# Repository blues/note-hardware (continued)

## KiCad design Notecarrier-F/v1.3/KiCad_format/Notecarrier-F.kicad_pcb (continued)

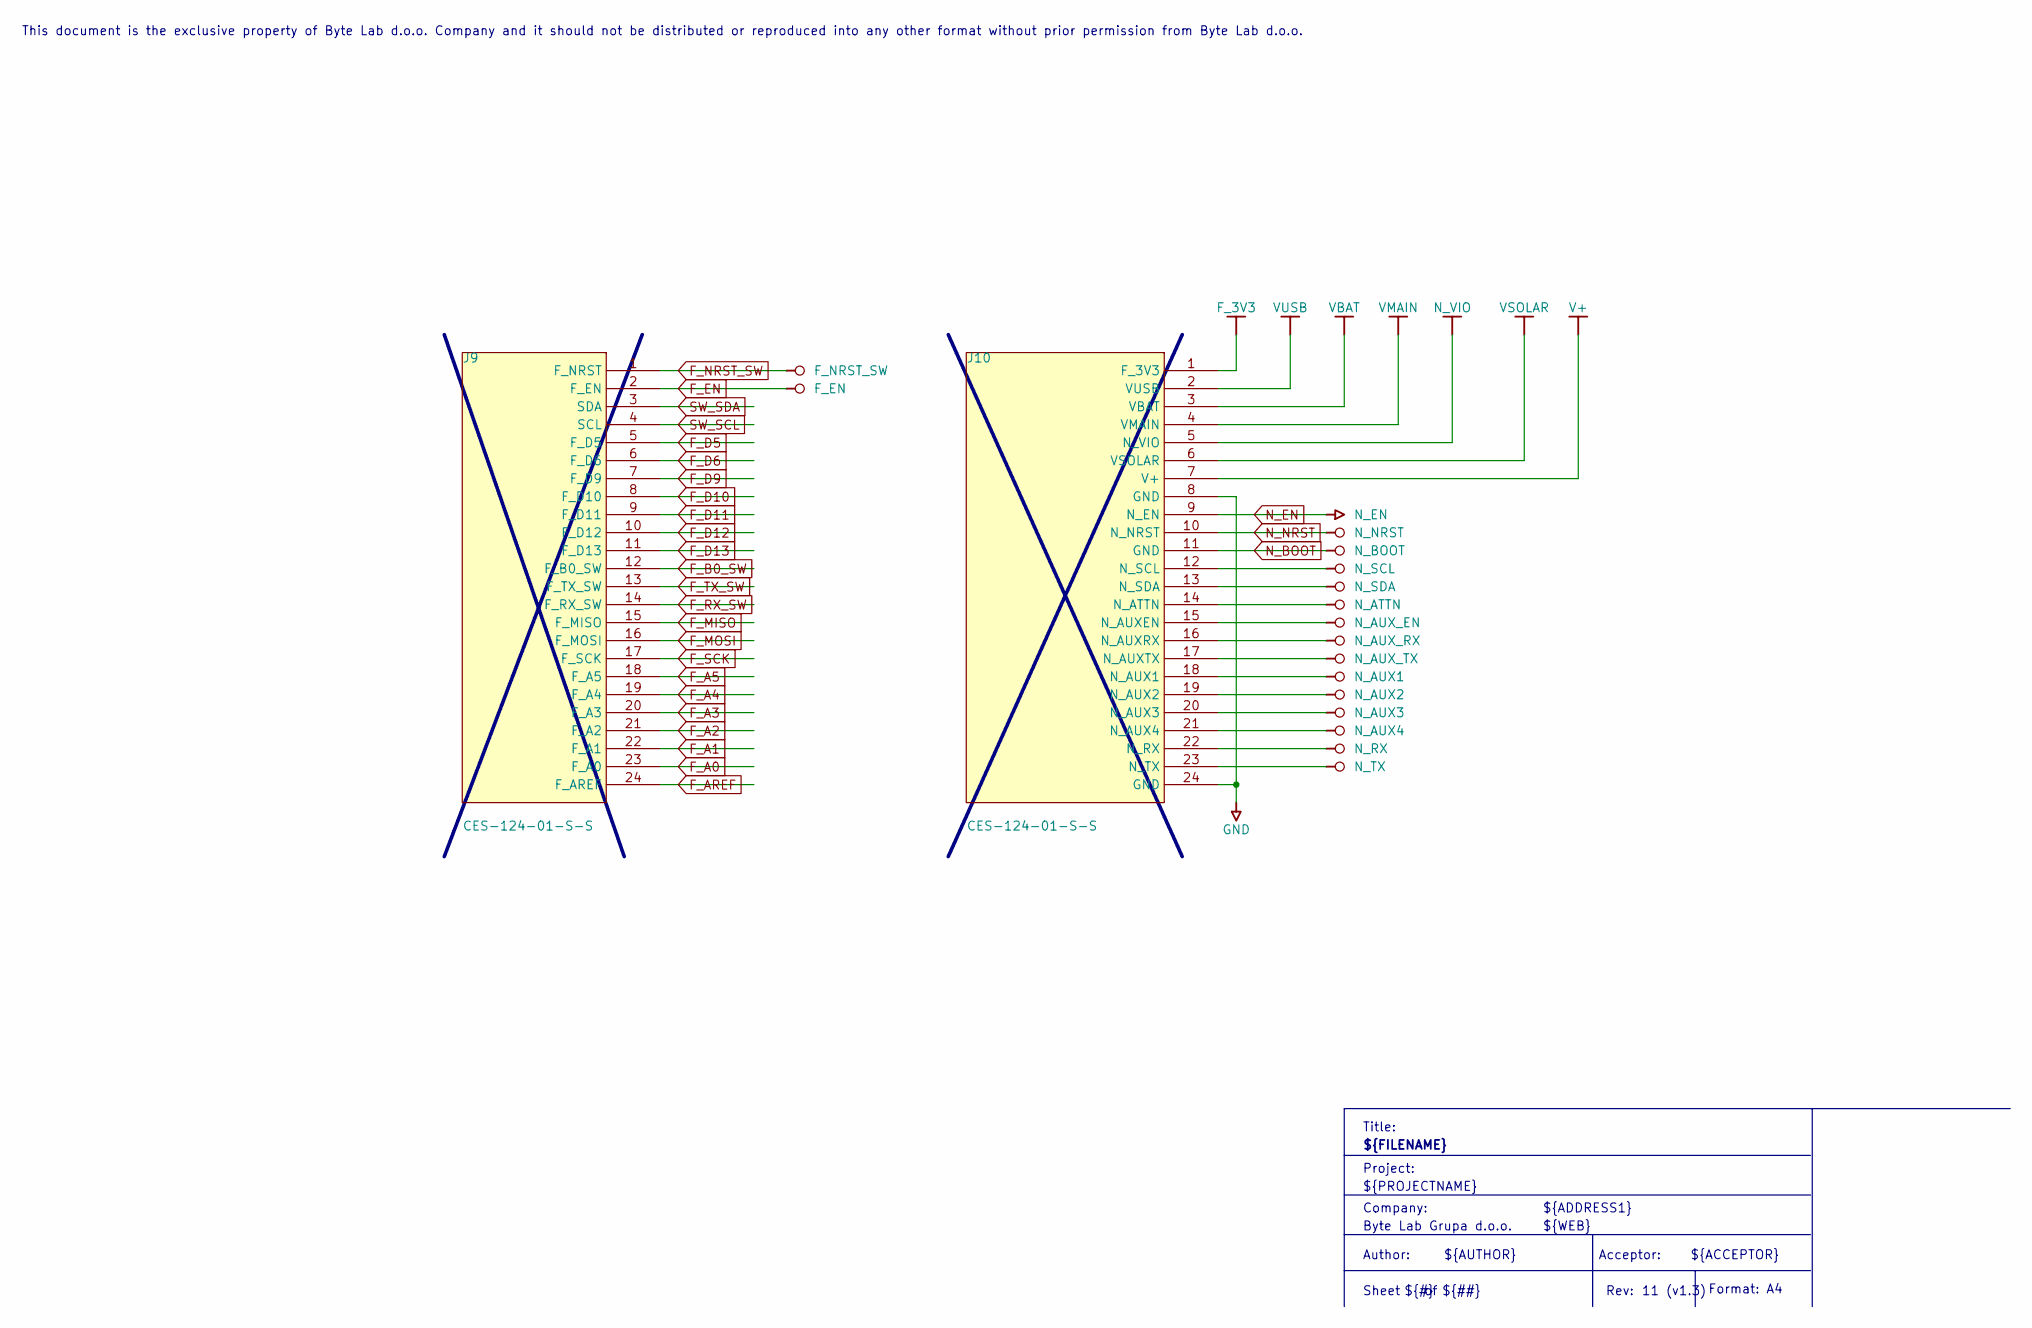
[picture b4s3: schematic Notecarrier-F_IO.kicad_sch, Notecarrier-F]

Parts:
J9, J10: CES-124-01-S-S; MANUFACTURER PART NUMBER CES-124-01-S-S

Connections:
F_3V3: J10.1 (F_3V3); also elsewhere on the board
F_A0: J9.23 (F_A0); also elsewhere on the board
F_A1: J9.22 (F_A1); also elsewhere on the board
F_A2: J9.21 (F_A2); also elsewhere on the board
F_A3: J9.20 (F_A3); also elsewhere on the board
F_A4: J9.19 (F_A4); also elsewhere on the board
F_A5: J9.18 (F_A5); also elsewhere on the board
F_AREF: J9.24 (F_AREF); also elsewhere on the board
F_B0_SW: J9.12 (F_B0_SW); also elsewhere on the board
F_D5: J9.5 (F_D5); also elsewhere on the board
F_D6: J9.6 (F_D6); also elsewhere on the board
F_D9: J9.7 (F_D9); also elsewhere on the board
F_D10: J9.8 (F_D10); also elsewhere on the board
F_D11: J9.9 (F_D11); also elsewhere on the board
F_D12: J9.10 (F_D12); also elsewhere on the board
F_D13: J9.11 (F_D13); also elsewhere on the board
F_EN: J9.2 (F_EN); also elsewhere on the board
F_MISO: J9.15 (F_MISO); also elsewhere on the board
F_MOSI: J9.16 (F_MOSI); also elsewhere on the board
F_NRST_SW: J9.1 (F_NRST); also elsewhere on the board
F_RX_SW: J9.14 (F_RX_SW); also elsewhere on the board
F_SCK: J9.17 (F_SCK); also elsewhere on the board
F_TX_SW: J9.13 (F_TX_SW); also elsewhere on the board
GND: J10.8 (GND), J10.24 (GND); also elsewhere on the board
N_ATTN: J10.14 (N_ATTN); also elsewhere on the board
N_AUX1: J10.18 (N_AUX1); also elsewhere on the board
N_AUX2: J10.19 (N_AUX2); also elsewhere on the board
N_AUX3: J10.20 (N_AUX3); also elsewhere on the board
N_AUX4: J10.21 (N_AUX4); also elsewhere on the board
N_AUX_EN: J10.15 (N_AUXEN); also elsewhere on the board
N_AUX_RX: J10.16 (N_AUXRX); also elsewhere on the board
N_AUX_TX: J10.17 (N_AUXTX); also elsewhere on the board
N_BOOT: J10.11 (GND); also elsewhere on the board
N_EN: J10.9 (N_EN); also elsewhere on the board
N_NRST: J10.10 (N_NRST); also elsewhere on the board
N_RX: J10.22 (N_RX); also elsewhere on the board
N_SCL: J10.12 (N_SCL); also elsewhere on the board
N_SDA: J10.13 (N_SDA); also elsewhere on the board
N_TX: J10.23 (N_TX); also elsewhere on the board
N_VIO: J10.5 (N_VIO); also elsewhere on the board
SW_SCL: J9.4 (SCL); also elsewhere on the board
SW_SDA: J9.3 (SDA); also elsewhere on the board
V+: J10.7 (V+); also elsewhere on the board
VBAT: J10.3 (VBAT); also elsewhere on the board
VMAIN: J10.4 (VMAIN); also elsewhere on the board
VSOLAR: J10.6 (VSOLAR); also elsewhere on the board
VUSB: J10.2 (VUSB); also elsewhere on the board

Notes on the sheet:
${AUTHOR}
${#}
${PROJECTNAME}
Title:
Author:
Sheet
Company:
${##}
Format: A4
Project:
${ACCEPTOR}
${ADDRESS1}
${REVISION}
This document is the exclusive property of Byte Lab d.o.o. Company and it should not be distributed or reproduced into any other format without prior permission from Byte Lab d.o.o.
${FILENAME}
Rev:
${COMPANY}
${WEB}
Acceptor:

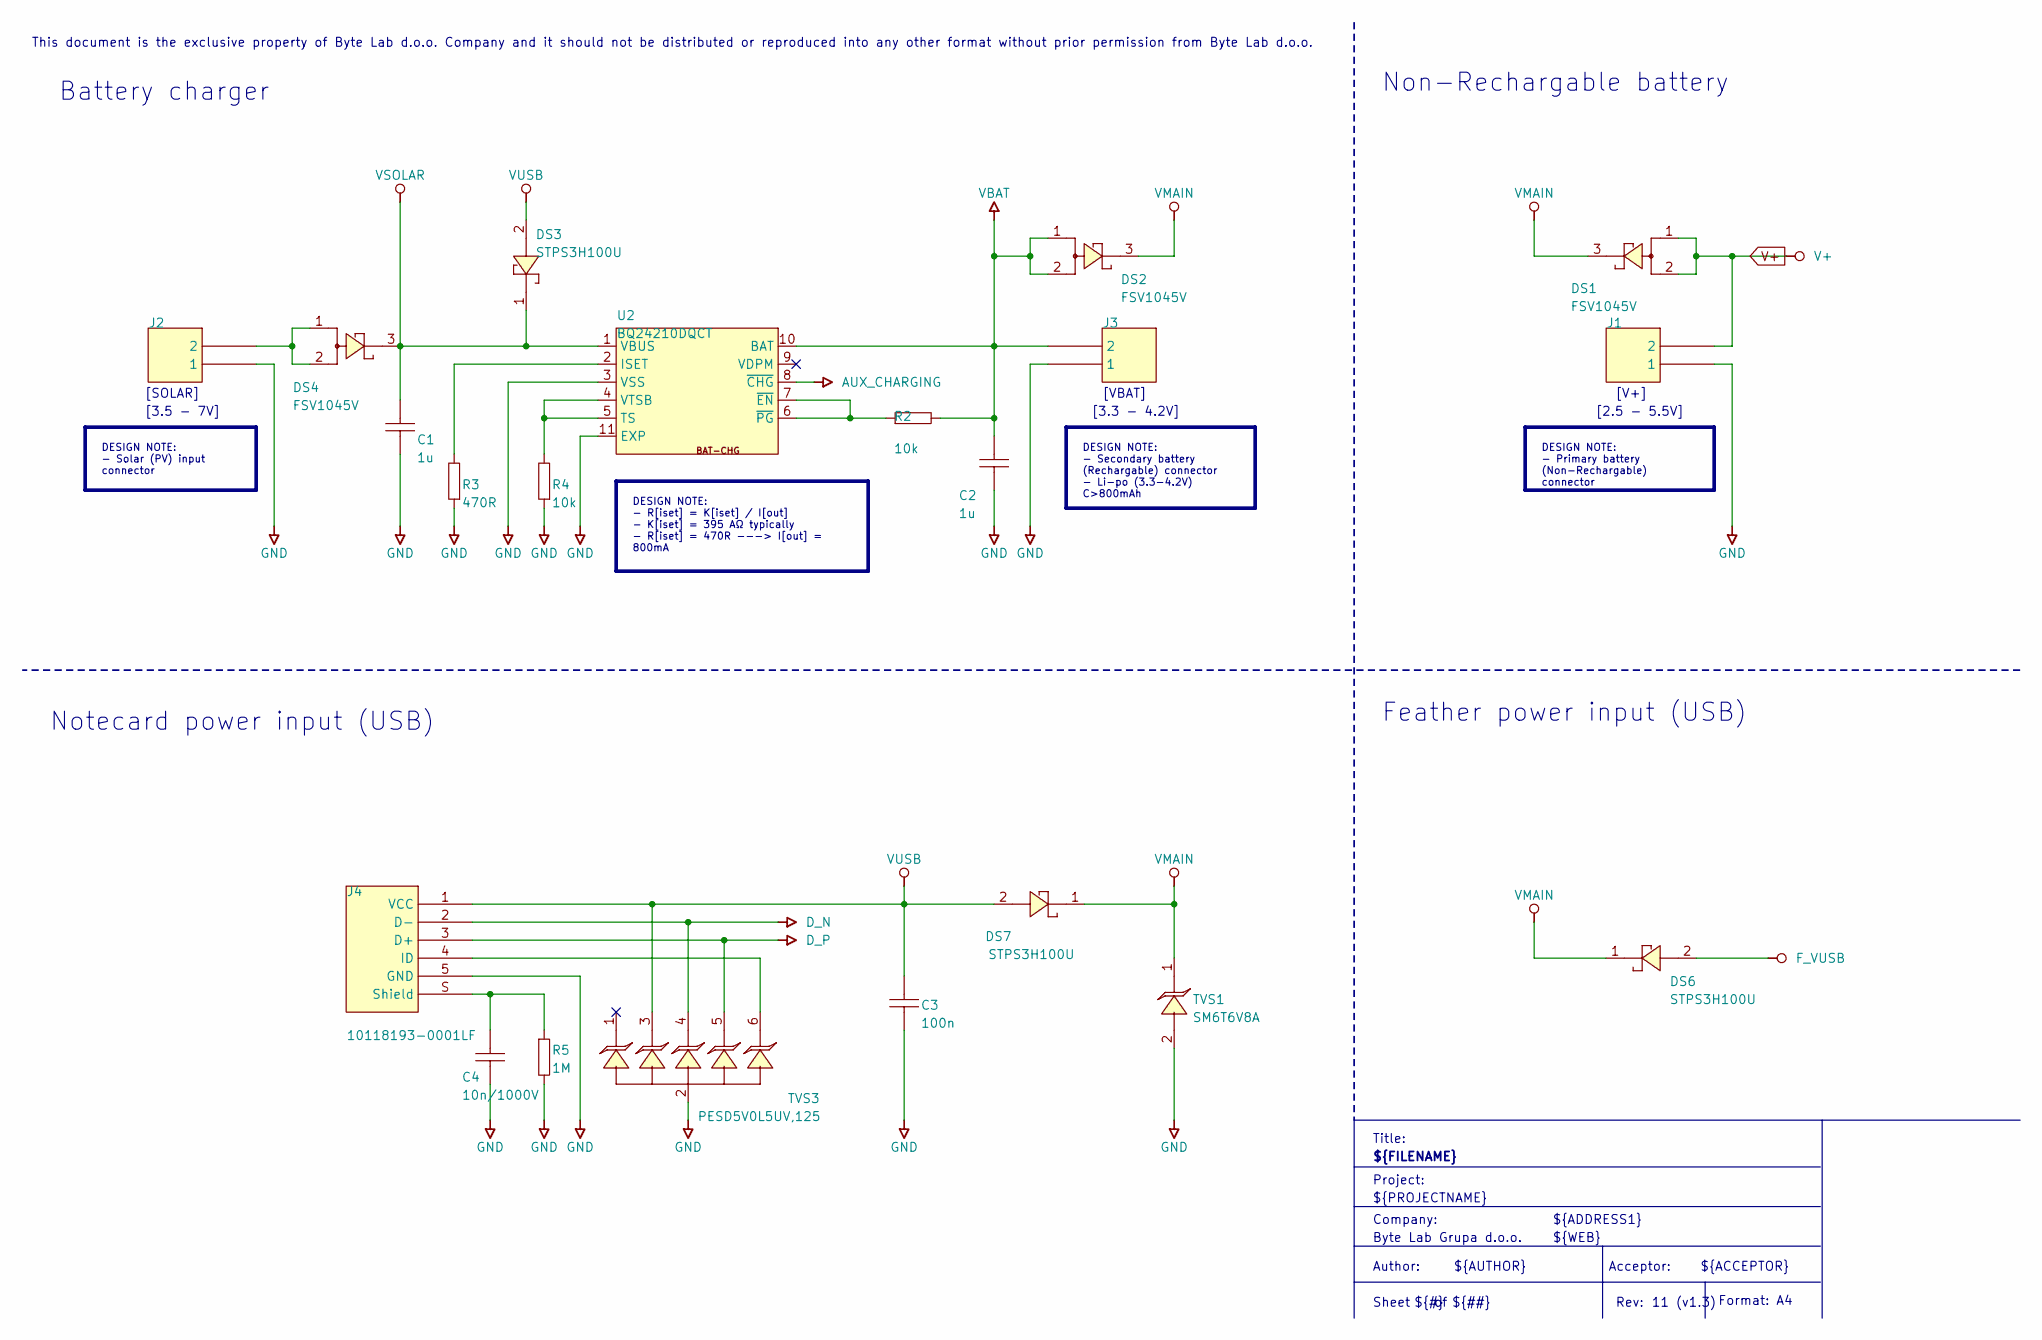
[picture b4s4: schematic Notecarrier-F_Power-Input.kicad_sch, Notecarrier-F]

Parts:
C1, C2: 1u; C-0603; MANUFACTURER PART NUMBER CC0603KRX5R8BB105
C3: 100n; C-0402; MANUFACTURER PART NUMBER N/A
C4: 10n/1000V; C-1206; MANUFACTURER PART NUMBER CS1206KKX7RCBB103
DS1, DS2, DS4: FSV1045V; TO277-3; MANUFACTURER PART NUMBER FSV1045V
DS3, DS6, DS7: STPS3H100U; SMB; MANUFACTURER PART NUMBER STPS3H100U
J1, J2, J3: S2BPHSM4TBLFSN; JST S2B-PH-SM4-TB; MANUFACTURER PART NUMBER S2B-PH-SM4-K-TB (LF)(SN)
J4: 10118193-0001LF; FCI USB 10118193-0001LF; MANUFACTURER PART NUMBER 10118193-0001LF
R2, R4: 10k; R-0402; MANUFACTURER PART NUMBER N/A
R3: 470R; R-0402; MANUFACTURER PART NUMBER N/A
R5: 1M; R-1206; MANUFACTURER PART NUMBER N/A
TVS1: SM6T6V8A; SMB; MANUFACTURER PART NUMBER SM6T6V8A
TVS3: PESD5V0L5UV,125; SOT666; MANUFACTURER PART NUMBER PESD5V0L5UV,125
U2: BQ24210DQCT; WSON10-EXP; MANUFACTURER PART NUMBER BQ24210DQCT

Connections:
AUX_CHARGING: U2.8 (~CHG); also elsewhere on the board
D_N: J4.2 (D-), TVS3.4 (C4); also elsewhere on the board
D_P: J4.3 (D+), TVS3.5 (A5); also elsewhere on the board
F_VUSB: DS6.2 (A); also elsewhere on the board
GND: C1.1, C2.1, C3.2, C4.2, J1.1, J2.1, J3.1, J4.5 (GND), R3.1, R4.1, R5.2, TVS1.2 (A), TVS3.2 (A2), U2.3 (VSS), U2.11 (EXP); also elsewhere on the board
unnamed: DS4.1 (A1), DS4.2 (A2), J2.2
unnamed: J4.4 (ID), TVS3.6 (C6)
unnamed: C4.1, J4.S (Shield), R5.1
unnamed: R3.2, U2.2 (ISET)
unnamed: R4.2, U2.4 (VTSB), U2.5 (TS)
unnamed: R2.1, U2.6 (~PG), U2.7 (~EN)
V+: DS1.1 (A1), DS1.2 (A2), J1.2; also elsewhere on the board
VBAT: C2.2, DS2.1 (A1), DS2.2 (A2), J3.2, R2.2, U2.10 (BAT); also elsewhere on the board
VMAIN: DS1.3 (C), DS2.3 (C), DS6.1 (C), DS7.1 (C), TVS1.1 (C); also elsewhere on the board
VSOLAR: C1.2, DS3.1 (C), DS4.3 (C), U2.1 (VBUS); also elsewhere on the board
VUSB: C3.1, DS3.2 (A), DS7.2 (A), J4.1 (VCC), TVS3.3 (C3); also elsewhere on the board

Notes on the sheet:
${WEB}
Feather power input (USB)
Project:
Non-Rechargable battery
${ADDRESS1}
Format: A4
Battery charger
${PROJECTNAME}
[3.3 - 4.2V]
${ACCEPTOR}
[V+]
[2.5 - 5.5V]
${#}
${FILENAME}
Title:
Company:
Acceptor:
${##}
${REVISION}
[3.5 - 7V]
${AUTHOR}
Rev:
Sheet
Notecard power input (USB)
This document is the exclusive property of Byte Lab d.o.o. Company and it should not be distributed or reproduced into any other format without prior permission from Byte Lab d.o.o.
Author:
${COMPANY}
[VBAT]
[SOLAR]
DESIGN NOTE: - Solar (PV) input connector
DESIGN NOTE: - R[iset] = K[iset] / I[out] - K[iset] = 395 AΩ typically - R[iset] = 470R ---> I[out] = 800mA
DESIGN NOTE: - Primary battery (Non-Rechargable) connector
DESIGN NOTE: - Secondary battery (Rechargable) connector - Li-po (3.3-4.2V) C>800mAh

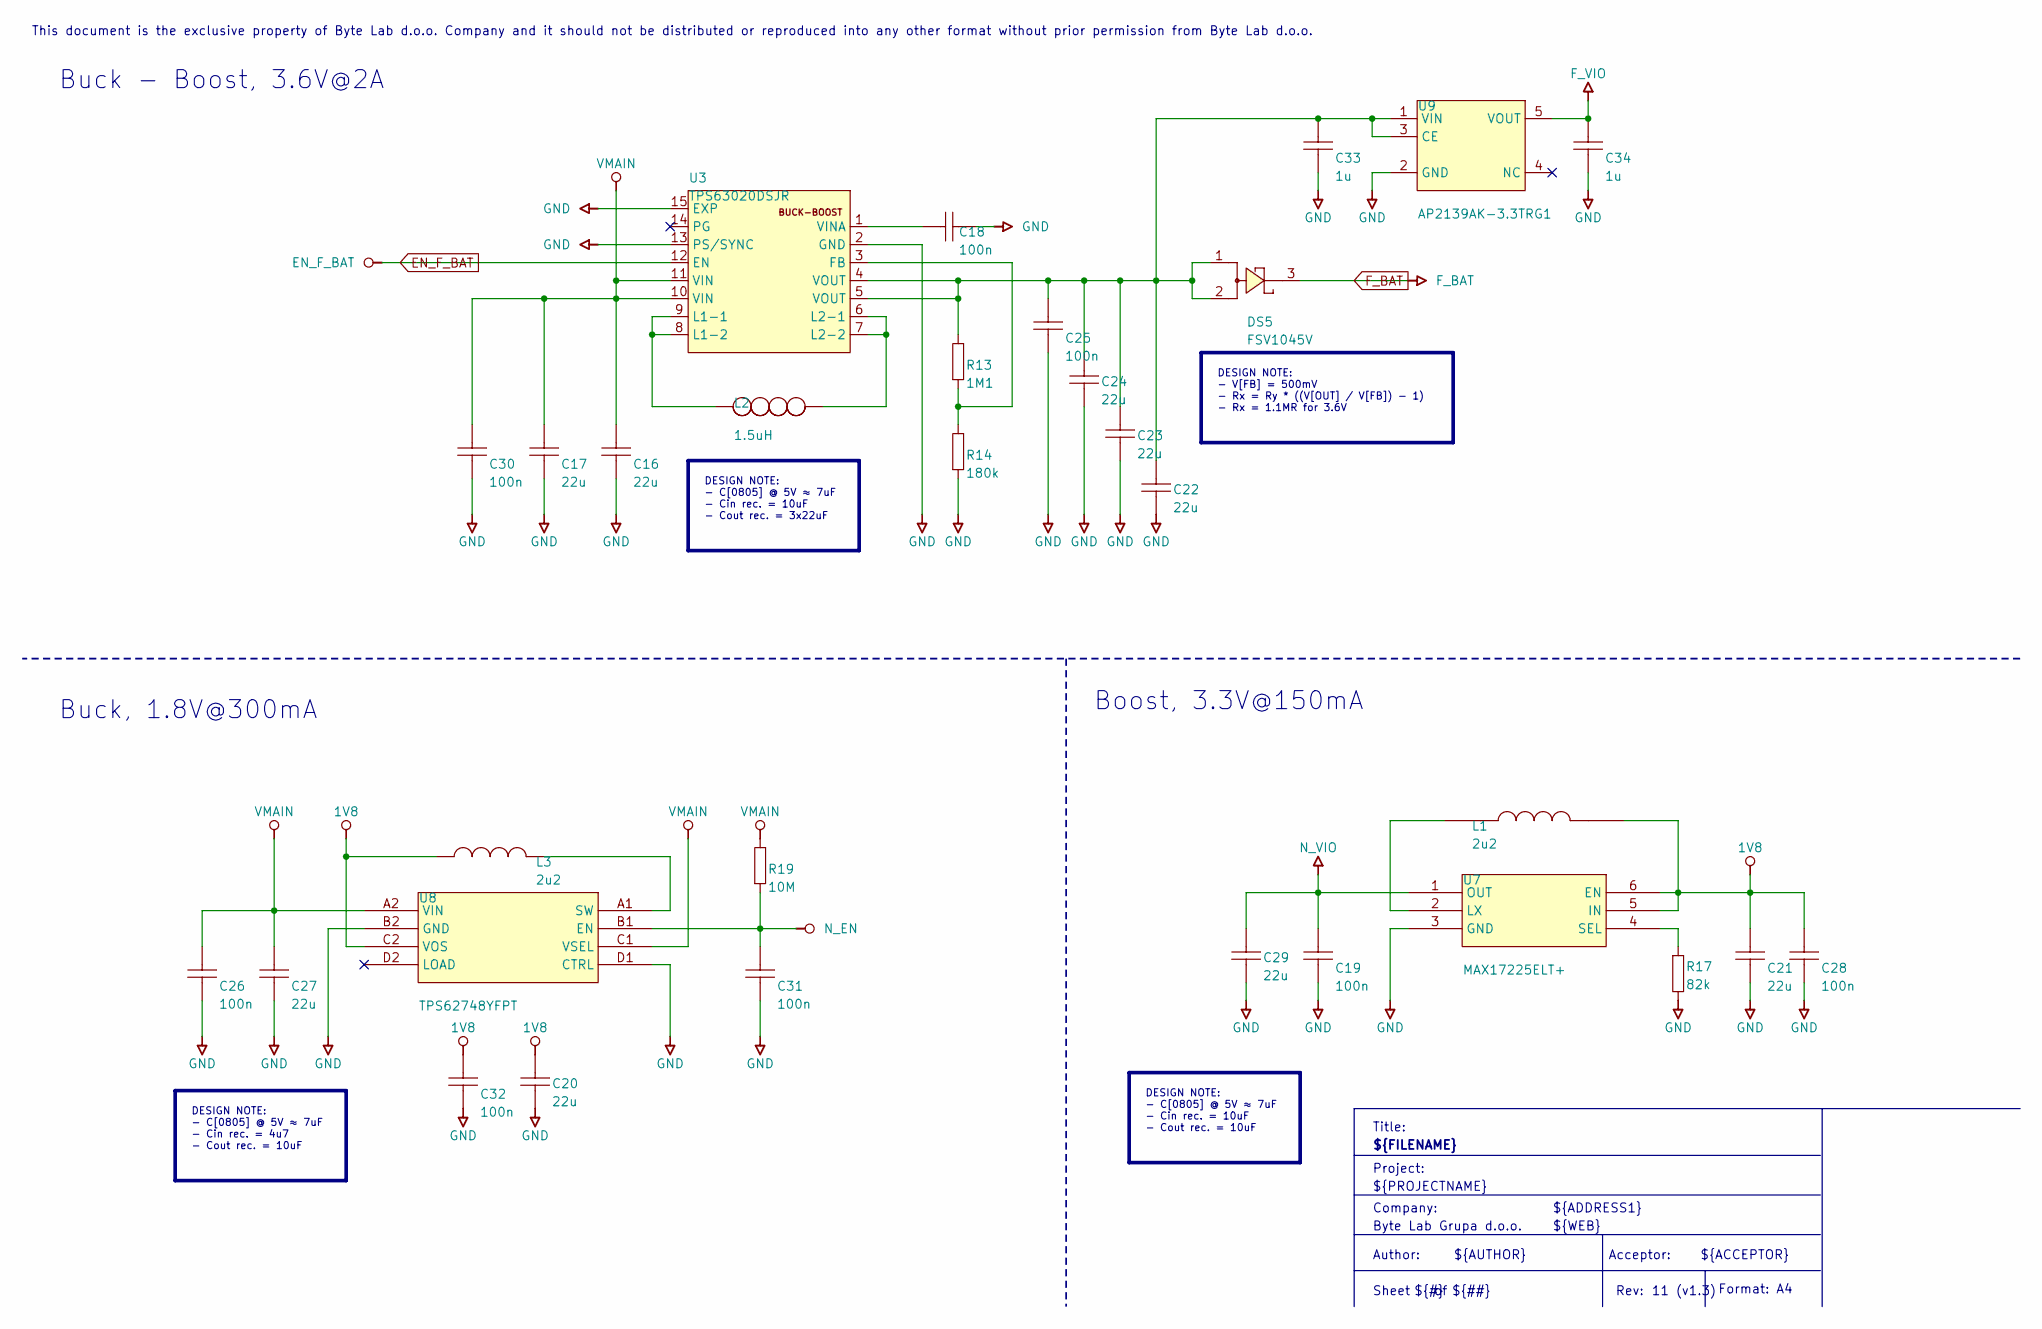
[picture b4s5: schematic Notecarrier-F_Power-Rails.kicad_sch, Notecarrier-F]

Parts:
C16, C17, C20, C21, C22, C23, C24, C27, C29: 22u; C-0805; MANUFACTURER PART NUMBER N/A
C18, C19, C25, C26, C28, C30, C31, C32: 100n; C-0402; MANUFACTURER PART NUMBER N/A
C33, C34: 1u; C-0603; MANUFACTURER PART NUMBER CC0603KRX5R8BB105
DS5: FSV1045V; TO277-3; MANUFACTURER PART NUMBER FSV1045V
L1: 2u2; IND_XFL4020-222MEC; MANUFACTURER PART NUMBE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 XFL4020-222MEC
L2: 1.5uH; VCHA042A-1R5MS6; MANUFACTURER PART NUMBER VCHA042A-1R5MS6
L3: 2u2; 1285AS-H-2R2M=P2-INDC2016X100N; MANUFACTURER PART NUMBER 1285AS-H-2R2M=P2
R13: 1M1; R-0402; MANUFACTURER PART NUMBER N/A
R14: 180k; R-0402; MANUFACTURER PART NUMBER N/A
R17: 82k; R-0402; MANUFACTURER PART NUMBER RC0402FR-0782KL
R19: 10M; R-0402; MANUFACTURER PART NUMBER N/A
U3: TPS63020DSJR; TI PVSON-14 DSJ; MANUFACTURER PART NUMBER TPS63020DSJR
U7: MAX17225ELT+; MAX17225ELT+UDFN; MANUFACTURER PART NUMBER MAX17225ELT+
U8: TPS62748YFPT; TPS62748YFPT-DSBGA4x2; MANUFACTURER PART NUMBER TPS62748YFPT
U9: AP2139AK-3.3TRG1; SOT-23-5(M5); MANUFACTURER PART NUMBER AP2139AK-3.3TRG1

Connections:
1V8: C20.1, C21.2, C28.2, C32.2, L1.2, L3.1, U7.5 (IN), U7.6 (EN), U8.C2 (VOS)
EN_F_BAT: U3.12 (EN); also elsewhere on the board
F_BAT: DS5.3 (C); also elsewhere on the board
F_VIO: C34.2, U9.5 (VOUT); also elsewhere on the board
GND: C16.1, C17.1, C18.1, C19.1, C20.2, C21.1, C22.2, C23.2, C24.2, C25.1, C26.1, C27.1, C28.1, C29.2, C30.1, C31.1, C32.1, C33.1, C34.1, R14.1, R17.2, U3.2 (GND), U3.13 (PS/SYNC), U3.15 (EXP), U7.3 (GND), U8.B2 (GND), U8.D1 (CTRL), U9.2 (GND); also elsewhere on the board
N_EN: C31.2, R19.1, U8.B1 (EN); also elsewhere on the board
N_VIO: C19.2, C29.1, U7.1 (OUT); also elsewhere on the board
unnamed: C22.1, C23.1, C24.1, C25.2, C33.2, DS5.1 (A1), DS5.2 (A2), R13.2, U3.4 (VOUT), U3.5 (VOUT), U9.1 (VIN), U9.3 (CE)
unnamed: L2.2 (A), U3.8 (L1-2), U3.9 (L1-1)
unnamed: L2.1 (C), U3.6 (L2-1), U3.7 (L2-2)
unnamed: R13.1, R14.2, U3.3 (FB)
unnamed: C18.2, U3.1 (VINA)
unnamed: L1.1, U7.2 (LX)
unnamed: R17.1, U7.4 (SEL)
unnamed: L3.2, U8.A1 (SW)
VMAIN: C16.2, C17.2, C26.2, C27.2, C30.2, R19.2, U3.10 (VIN), U3.11 (VIN), U8.A2 (VIN), U8.C1 (VSEL); also elsewhere on the board

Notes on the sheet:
Author:
${##}
This document is the exclusive property of Byte Lab d.o.o. Company and it should not be distributed or reproduced into any other format without prior permission from Byte Lab d.o.o.
${ACCEPTOR}
Buck - Boost, 3.6V@2A
Boost, 3.3V@150mA
${PROJECTNAME}
Format: A4
${#}
Title:
${AUTHOR}
Buck, 1.8V@300mA
Project:
${ADDRESS1}
Acceptor:
${COMPANY}
Rev:
${WEB}
Company:
Sheet
${FILENAME}
${REVISION}
DESIGN NOTE: - V[FB] = 500mV - Rx = Ry * ((V[OUT] / V[FB]) - 1) - Rx = 1.1MR for 3.6V
DESIGN NOTE: - C[0805] @ 5V ≈ 7uF - Cin rec. = 10uF - Cout rec. = 3x22uF
DESIGN NOTE: - C[0805] @ 5V ≈ 7uF - Cin rec. = 4u7 - Cout rec. = 10uF
DESIGN NOTE: - C[0805] @ 5V ≈ 7uF - Cin rec. = 10uF - Cout rec. = 10uF

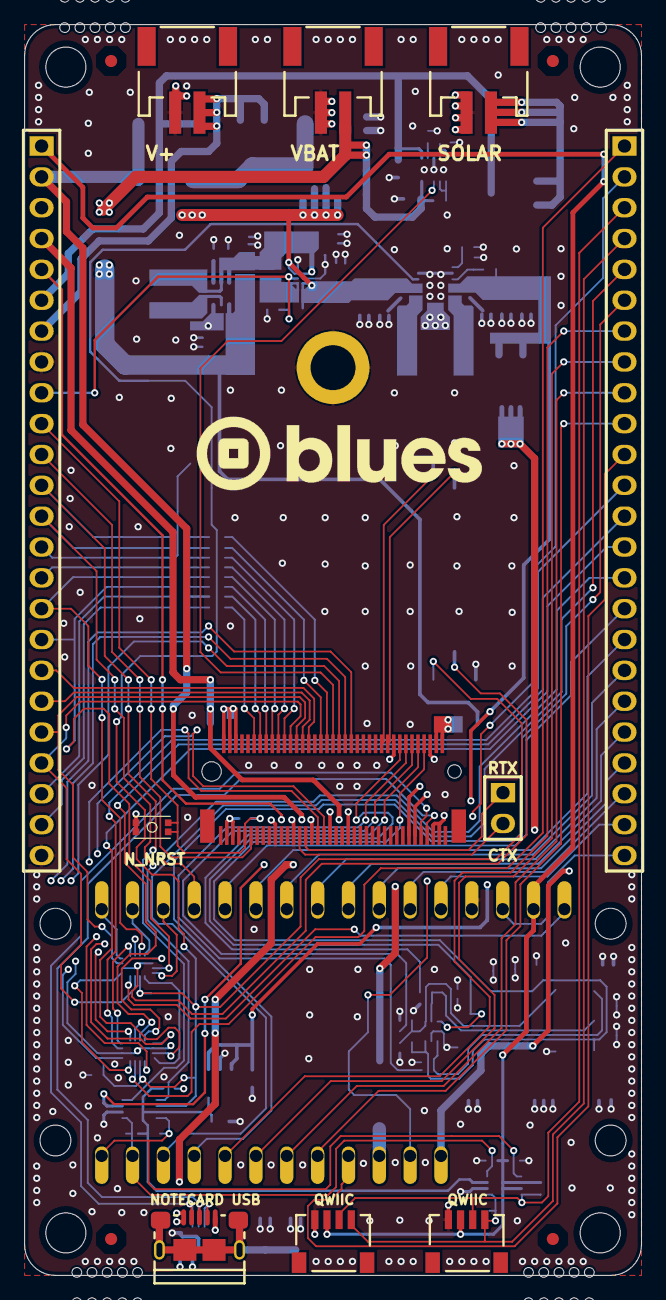
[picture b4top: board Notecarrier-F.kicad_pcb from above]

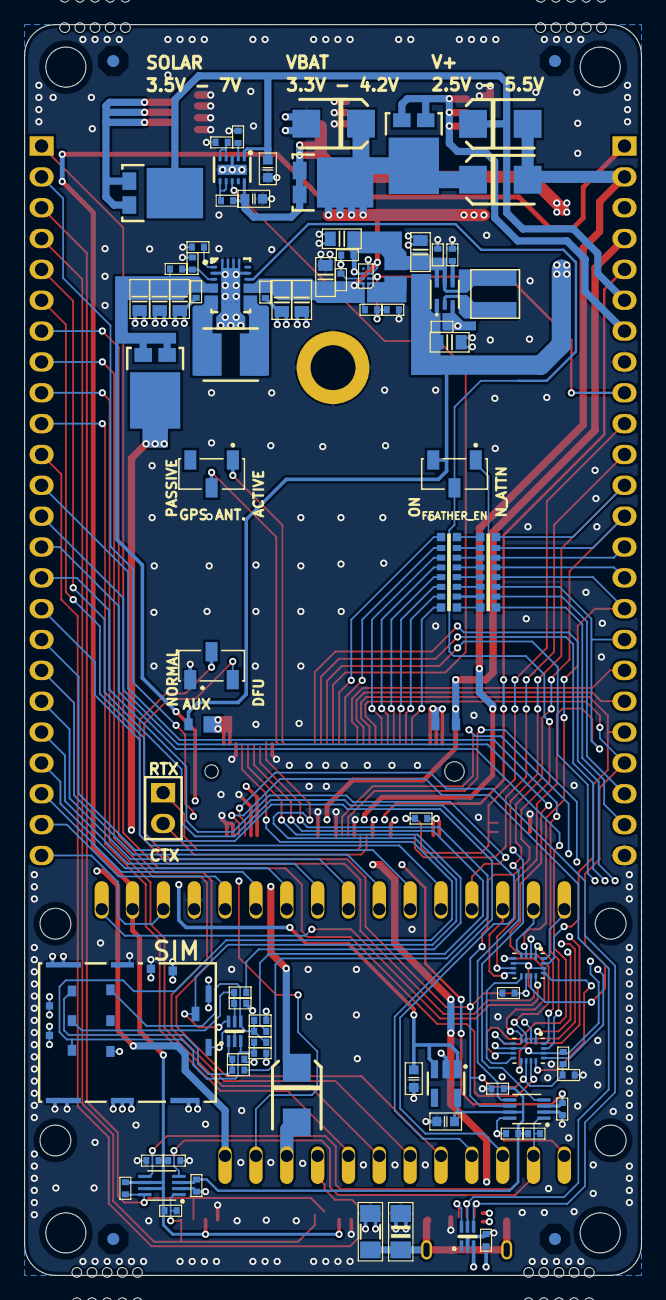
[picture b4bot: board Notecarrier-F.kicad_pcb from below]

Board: 4 copper layers, 50.8 x 103.0 mm, 153 parts (86 on the bottom side), 115 nets.

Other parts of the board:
FD1, FD2, FD3, FD4, FD5, FD6, FD7, FD8: Fiducial mark; Fiducial mark 1mm
H1, H2, H3, H4, H5, H6, H7, H8, H9, H10, H11, H12, H13, H14, H15, H16, H17, H18, H19, H20, H29, H30, H31, H32, H33, H34, H35, H36, H37, H38, H39, H40, H41, H42, H43, H44, H45, H46, H47, H48: NPTH_free_hole
H21, H22, H27, H28: NPTH_free_hole_3.3mm
H23, H24, H25, H26: NPTH_free_hole_2.54mm

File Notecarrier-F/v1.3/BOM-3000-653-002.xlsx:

|  | BOM-3000-653-002 |  |  | Notecarrier F
 |  | Project: |  |  | Notecarrier F
 |  | Module: |  |  | Notecarrier F
 |  | Variant: |  |  | Production
 |  | Report Date: |  | 45169 | 0.60902777777777783
 |  | Print Date: |  | 45169 | 45169.610375810182
 | # | BL Part Number | Item Name | Reference | Manufacturer | Manufacturer Part Number | Detail | Unit Of Measure | Quantity
 | 1 | 2006-845 | IC REG LINEAR 3.3V 0.25A | U9 | Diodes Incorporated | AP2139AK-3.3TRG1 | +3V3/0.25A | pcs | 1
 | 2 | 2007-480 | IC REG, Buck, 1.8V, 0.3A | U8 | Texas Instruments | TPS62748YFPT | 0.3A | pcs | 1
 | 3 | 2007-481 | IC REG, Boost, ADJ, 1A | U7 | Maxim Integrated | MAX17225ELT+ | 1A | pcs | 1
 | 4 | 2007-457 | IC SW DPDTX2 500MOHM 16MINIQFN | U5, U6 | Vishay Siliconix | DGQ2788AEN-T1-GE4 | 2XDPDT | pcs | 2
 | 5 | 2002-405 | IC REG BUCK BST ADJ 3.5A QFN-14 | U3 | Texas Instruments | TPS63020DSJR |  | pcs | 1
 | 6 | 2005-527 | IC, Battery charger, Li-Ion, 1cell | U2 | Texas Instruments | BQ24210DQCT |  | pcs | 1
 | 7 | 2007-455 | IC TRANSLTR BIDIRECTIONAL 8VSSOP | U1, U4 | Texas Instruments | TXS0102DCUR | 2CH | pcs | 2
 | 8 | 2007-452 | Diode TVS array, 5CH, UNI, 6.4V/12V | TVS2, TVS3 | NXP Semiconductors | PESD5V0L5UV,125 | 5V | pcs | 2
 | 9 | 2007-453 | DIODE TVS, UNI, 6.45V/13.4V | TVS1 | STMicroelectronics | SM6T6V8A | 5.8V | pcs | 1
 | 10 | 2007-124 | SW TACT, SPST, NO, 15VDC, 0.02A | SW2 | Panasonic | EVP-BB2A9B000 | SPST | pcs | 1
 | 11 | 2007-456 | SWITCH SLIDE SPDT 100MA 6V | SW1, SW3, SW4 | Nidec | CJS-1200TA | SPDT | pcs | 3
 | 12 | 2002-832 | Resistor, 10M, ±1%, 0.063W, 0402 | R19 | Yageo | RC0402FR-0710ML | 10M | pcs | 1
 | 13 | 2000-727 | Resistor 100k 1% 0402 | R18 | Yageo | RC0402FR-07100KL | 100k | pcs | 1
 | 14 | 2001-566 | Resistor, 82k, ±1%, 0.063W, 0402 | R17 | ROYAL OHM | 0402WGF8202TCE | 82k | pcs | 1
 | 15 | 2001-422 | Resistor, 180k, ±1%, 0.063W, 0402 | R14 | Yageo | RC0402FR-07180KL | 180k | pcs | 1
 | 16 | 2000-730 | Resistor, 1M1, ±1%, 0.063W, 0402 | R13 | Bourns Inc. | CR0402-FW-1104GLF | 1M1 | pcs | 1
 | 17 | 2001-170 | Resistor, 22R, ±1%, 0.063W, 0402 | R7, R8, R9 | Yageo | AC0402FR-0722RL | 22R | pcs | 3
 | 18 | 2001-157 | Resistor, 15k, ±1%, 0.63W, 0402 | R6 | ROYAL OHM | 0402WGF1502TCE | 15k | pcs | 1
 | 19 | 2001-438 | Resistor, 1M, ±1%, 0.25W, 1206 | R5 | Yageo | RE1206FRE071ML | 1M | pcs | 1
 | 20 | 2001-420 | Resistor, 470R, ±1%, 0.063W, 0402 | R3 | Yageo | RC0402FR-13470RL | 470R | pcs | 1
 | 21 | 2000-729 | Resistor 10k 1% 0402 | R2, R4, R10, R15, R16 | Yageo | RC0402FR-0710KL | 10k | pcs | 5
 | 22 | 2007-472 | Resistor array, 100R, 8way, ±5%, 63mW, 2506 | R1, R20 | CTS Resistor Products | 742C163101JP | 100R | pcs | 2
 | 23 | 2200-814 | PCB Notecarrier F | PCB1 |  |  |  | pcs | 1
 | 24 | 6020-113 | Round standoff, Steel(Sn), 5.1mm | OBJ1 | Wurth Elektronik | 9774025151R | M2.5 | pcs | 1
 | 25 | 2007-464 | Conn Receptacle, 1x12, 2.54mm, Gold plated | MOD1R | SAMTEC | CES-112-01-L-S | 12WAY | pcs | 1
 | 26 | 2007-463 | Conn Receptacle, 1x16, 2.54mm, Gold plated | MOD1L | SAMTEC | CES-116-01-L-S | 16WAY | pcs | 1
 | 27 | 2007-482 | Inductor, Shielded, 2u2, ±20%, 1.5A | L3 | Murata Electronics | 1285AS-H-2R2M=P2 | 2u2 | pcs | 1
 | 28 | 2007-451 | Inductor, Unshielded, 1u5, ±20%, 5.3A | L2 | Delta Electronics | VCHA042A-1R5MS6 | 1u5 | pcs | 1
 | 29 | 2007-483 | Inductor, Shielded, 2u2, ±20%, 3.7A | L1 | Coilcraft | XFL4020-222MEC | 2u2 | pcs | 1
 | 30 | 2002-058 | CONN HEADER SH SIDE 4POS 1MM SMD | J7, J8 | JST | SM04B-SRSS-TB | 4WAY | pcs | 2
 | 31 | 2007-460 | CONN M.2 FMALE 67POS 0.020 GOLD | J6 | Amphenol | MDT420E03001 |  | pcs | 1
 | 32 | 2007-458 | NANO SIM CARD CONNECTOR | J5 | JAE Electronics | SF72S006VBDR2500 | SIM nano | pcs | 1
 | 33 | 2007-454 | CONN RCPT USB2.0 MICRO B SMD R/A | J4 | Amphenol | 10118193-0001LF | USB Micro | pcs | 1
 | 34 | 2007-662 | Conn Header, 1x2, 2.0mm, R/A | J1, J2, J3 | JST | S2B-PH-SM4-K-TB(LF)(SN) | 2way | pcs | 3
 | 35 | 2007-469 | FUSE, 32VAC/DC, 3.5A, Fast | F2 | Bourns Inc. | 046703.5NR | 3.5A | pcs | 1
 | 36 | 2007-468 | FUSE, 32VDC, 1.5A, Fast | F1 | Bourns Inc. | SF-0603F150-2 | 1.5A | pcs | 1
 | 37 | 2007-711 | Diode Schottky, 100V, 3A | DS3, DS6, DS7 | STMicroelectronics | STPS3H100U | 100V/3A | pcs | 3
 | 38 | 2007-712 | Diode Schottky, 45V, 10A | DS1, DS2, DS4, DS5 | onsemi | FSV1045V | 45V/10A | pcs | 4
 | 39 | 100275 | Notecarrier F | DOC1 |  |  |  | pcs | 1
 | 40 | 2006-222 | Capacitor ceramic, 22u, ±10%, X5R, 16V, 0805 | C16, C17, C20, C21, C22, C23, C24, C27, C29 | Samsung | CL21A226KOQNNNE | 22u/16V | pcs | 9
 | 41 | 2001-377 | Capacitor ceramic, 33p, ±5%, C0G, 50V, 0402 | C6, C7, C8 | Samsung | CL05C330JB5NNNC | 33p/50V | pcs | 3
 | 42 | 2007-449 | Capacitor ceramic, 10n, ±10%, X7R, 1000V, 1206 | C4 | Yageo | CS1206KKX7RCBB103 | 10n/1000V | pcs | 1
 | 43 | 2000-908 | Capacitor ceramic 100n ±10% X7R 16V 0402 | C3, C5, C9, C10, C11, C12, C13, C14, C15, C18, C19, C25, C26, C28, C30, C31, C32 | Murata | GCM155R71C104KA55D | 100n/16V | pcs | 17
 | 44 | 2006-223 | Capacitor ceramic, 1u, ±10%, X5R, 25V, 0603 | C1, C2, C33, C34 | Yageo | CC0603KRX5R8BB105 | 1u/25V | pcs | 4
 | 45 | 6000-168 | Machine screw, SS A2, Philips(PH1), Cheese head, DIN7985 | ASS1 | KRAFTBERG | M2.5X4/D7985-A2 | M2.5 | pcs | 1
 | 46 | 2007-465 | Conn Receptacle, 1x24, 2.54mm, Gold plated | J9, J10 | SAMTEC | CES-124-01-S-S | 24WAY | pcs | 2
 | Approved |  |  |  | Notes |  |  | Total | 96

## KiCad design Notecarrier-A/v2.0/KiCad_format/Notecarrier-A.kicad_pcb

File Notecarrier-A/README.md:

# Notecarrier A

  - Schematics
  - Bills of material
  - PCB layouts and Gerber files
  - Dimensioned drawings
  - 3D models
  - KiCad design files ([v2.0/KiCad_format](v2.0/KiCad_format); the v2.0 port is the canonical KiCad reference — v2.3 is an OrCAD/Allegro revision with no importable sources, and its KiCad port is [committed but incomplete and not usable](v2.3/KiCad_format/STATUS-INCOMPLETE.md))

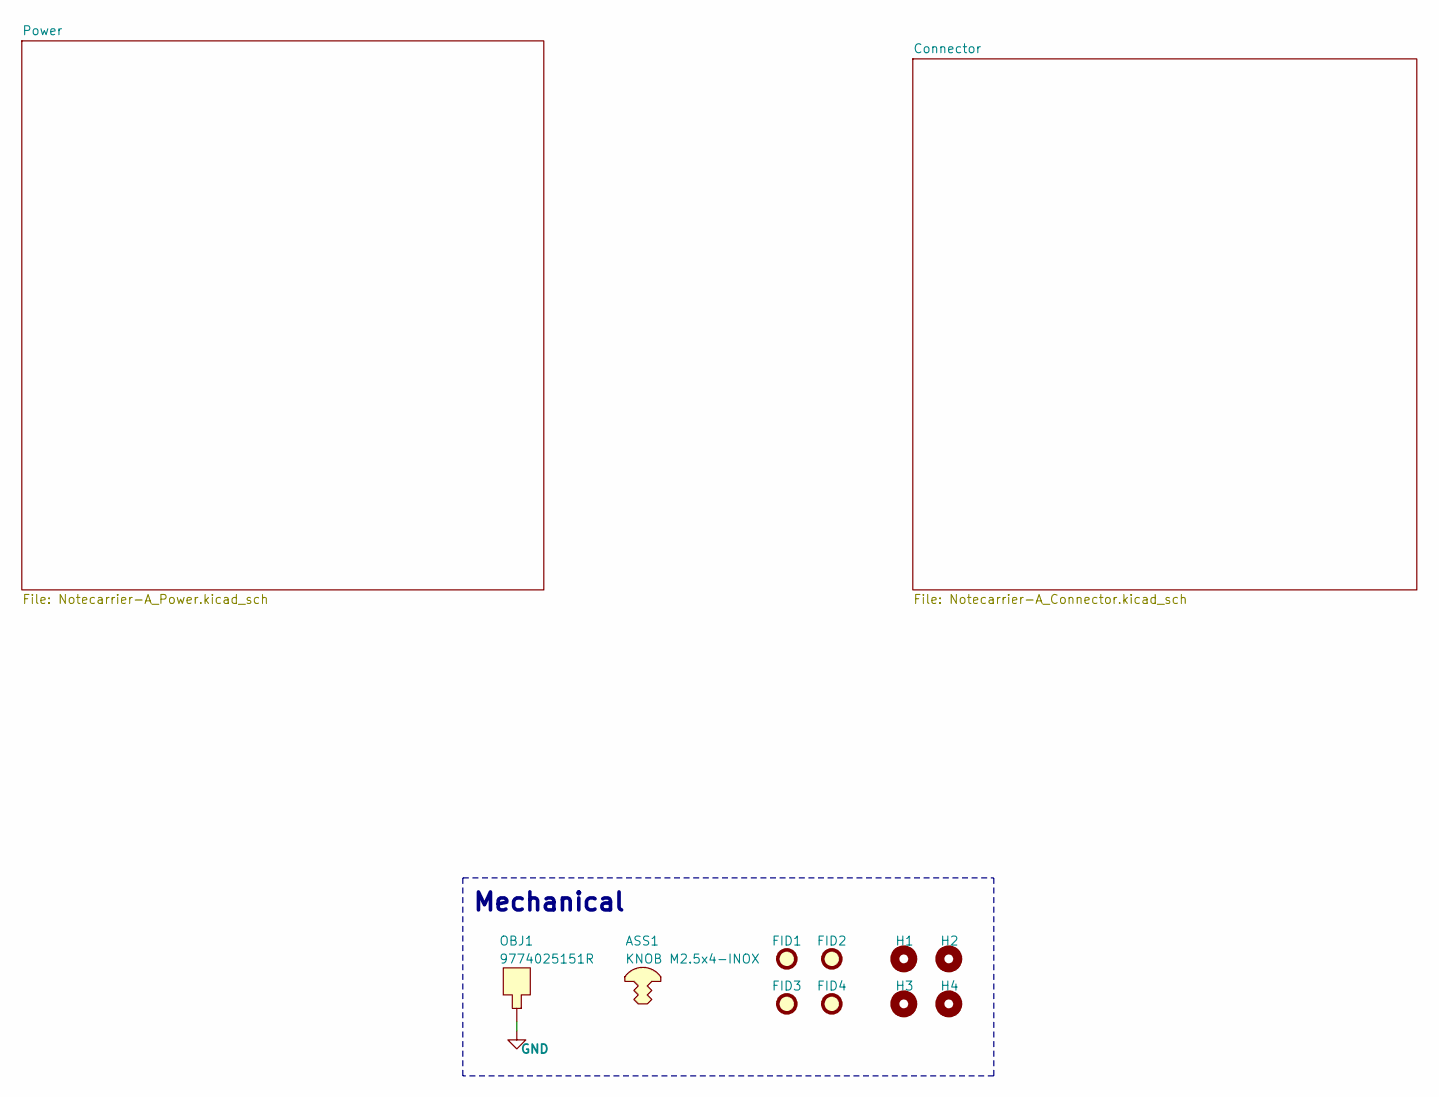
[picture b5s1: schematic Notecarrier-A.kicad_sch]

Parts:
ASS1: KNOB M2.5x4-INOX
FID1, FID2, FID3, FID4: TPS; FIDUCIAL_MIN-CLEARANCE
H1, H2, H3, H4: MountingHole; FORO-0330-U
OBJ1: 9774025151R; DIST-WASMSIM0250

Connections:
GND: OBJ1.1; also elsewhere on the board

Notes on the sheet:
Mechanical
